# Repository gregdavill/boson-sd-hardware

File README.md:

# bosonFrameGrabber

	Project Stage: Basic MVP achieved

A Small FPGA based board. Designed to connect to a FLIR Boson Camera, and save images from the camera to a microSD card.

hw 1_02 is the latest functionaly hardware that fits just behind the back of the Boson. (Pictured Above)

## Project Status:
 + hw 1_01 working (reached limitations of FPGA)
 + hw 1_02 status
   + designed/assembled prototypes
   + Working on Firmware on a softcore riscv CPU. 
   + Basic capture system implmented in rtl.
   + Basic driver for SD card access using FatFS and SD-controller.

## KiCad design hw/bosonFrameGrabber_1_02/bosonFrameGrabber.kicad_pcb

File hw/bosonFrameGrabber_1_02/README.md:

# bosonFrameGrabber v1.02

	Project Stage: Still in Development

A Small FPGA based board. Designed to connect to a FLIR Boson Camera, and save images from the camera to a microSD card.

## Hardware

* ECP5 in csBGA285 package
* 64Mb/128Mb HyperRAM
* 8Mb QSPI Memory
* MicroSD socket
* 24Mhz MEMs Oscillator
* JST GH SM06 locking Data/Power connector
* JTAG exposed via pogo pin pads.
* 2x 5V tolerant I/Os on connector
* 1x LED

Prototype Limitations:
* 3.3V only! (Integrated LDOs handle FPGA rails, but input power is connected directly to the Boson)

## Prototype

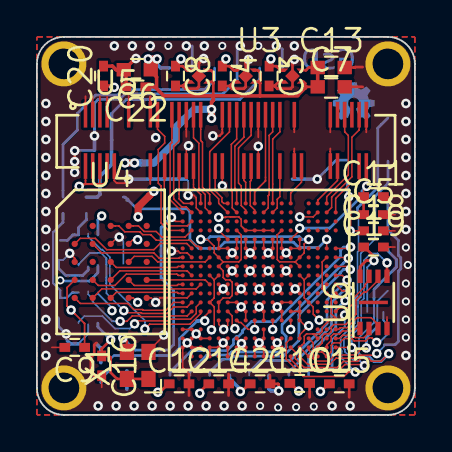
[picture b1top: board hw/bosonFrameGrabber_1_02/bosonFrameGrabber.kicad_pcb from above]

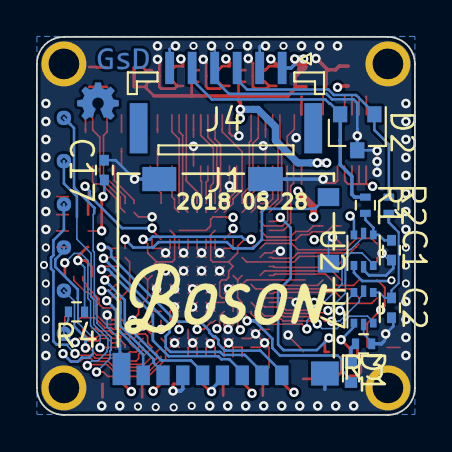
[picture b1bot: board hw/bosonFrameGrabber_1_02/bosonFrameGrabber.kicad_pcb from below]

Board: 4 copper layers, 21.0 x 21.0 mm, 40 parts (13 on the bottom side), 67 nets.

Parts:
C1, C2: 100pF; C_0402
C3, C4, C8: 1uF; C_0402
C5, C9, C10, C11, C12, C14, C15, C16, C17, C18, C19, C20, C21, C22: 100nF; C_0402
C6, C7, C13: 10uF; C_0603
D1: LED; LED_0402
D2: D_TVS_x2_AAC; SOT-23
J1: JST GH Series; JST_GH_BM06B-GHS-TBT_06x1.25mm_Straight
J4: MicroSD; 1040310811
R1, R2: 100R; R_0402
R3, R4: 10k; R_0402
U1: TLV70725; X2SON
U2, U7: SN74LVC1T45; SOT-666
U3: ECP5U25; csBGA_132
U4: S27KS0641; BGA_24
U5: Boson; DF40_80Pin
U6: AT25SF081; DFN-8-1EP_3x2mm_Pitch0.5mm
U8: TLV71718; X2SON
U9: TLV73311; X2SON
X1: ASDMB; Oscillator_SMD_SeikoEpson_SG210-4pin_2.5x2.0mm

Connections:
16MHZ_IN: U3.C1, X1.3
+1V1: C8.1, C10.1, C14.1, C17.1, C18.1, C20.1, U3.D8, U3.D9, U3.D10, U3.D11, U3.J4, U3.J5, U3.J14, U3.J15, U3.M4, U3.M15, U3.P7, U3.P9, U3.P11, U9.1
+1V8: C4.1, C9.1, C12.1, C16.1, U2.1, U3.D7, U3.D12, U3.G5, U3.G14, U3.H5, U3.H14, U3.M5, U3.N5, U4.B4, U4.D1, U4.E4, U7.1, U8.1, X1.1, X1.4
+2V5: C3.1, C5.1, C11.1, C15.1, U1.1, U3.E6, U3.E13, U3.N6, U3.P13
+3V3: C6.1, C7.1, C13.1, C19.1, C21.1, C22.1, J1.1, J4.4, R4.1, U1.3, U1.4, U2.6, U3.M14, U3.N13, U3.N14, U3.P14, U3.T14, U5.2, U5.4, U5.6, U5.8, U6.8, U7.6, U8.3, U8.4, U9.3, U9.4
BOSON_CK: U3.A11, U5.55
BOSON_DATA0: U3.B17, U5.77
BOSON_DATA1: U3.A13, U5.62
BOSON_DATA2: U3.A9, U5.51
BOSON_DATA3: U3.B11, U5.56
BOSON_DATA4: U3.B2, U5.27
BOSON_DATA5: U3.A2, U5.28
BOSON_DATA6: U3.A3, U5.32
BOSON_DATA7: U3.B4, U5.31
BOSON_DATA8: U3.B1, U5.25
BOSON_DATA9: U3.A8, U5.46
BOSON_DATA10: U3.A7, U5.45
BOSON_DATA11: U3.B9, U5.48
BOSON_DATA12: U3.B8, U5.47
BOSON_DATA13: U3.B6, U5.41
BOSON_DATA14: U3.D1, U5.21
BOSON_DATA15: U3.A6, U5.38
BOSON_DATA_EN: U3.B18, U5.78
BOSON_EXTSYNC: U3.A16, U5.72
BOSON_HSYNC: U3.A17, U5.73
BOSON_RESET: U3.C2, U5.24
BOSON_RXD: U3.A4, U5.33
BOSON_TXD: U3.B7, U5.43
BOSON_VSYNC: U3.B10, U5.53
FPGA_RESET: R4.2, U3.T15, U3.V17
GND: C1.2, C2.2, C3.2, C4.2, C5.2, C6.2, C7.2, C8.2, C9.2, C10.2, C11.2, C12.2, C13.2, C14.2, C15.2, C16.2, C17.2, C18.2, C19.2, C20.2, C21.2, C22.2, D2.3, J1.2, J1.4, J1.6, J4.6, J4.9, J4.10, R3.1, U1.2, U2.2, U3.B3, U3.B16, U3.E5, U3.E7, U3.E8, U3.E9, U3.E10, U3.E11, U3.E12, U3.E14, U3.F5, U3.F6, U3.F7, U3.F8, U3.F9, U3.F10, U3.F11, U3.F12, U3.F13, U3.F14, U3.G2, U3.G6, U3.G7, U3.G8, U3.G9, U3.G10, U3.G11, U3.G12, U3.G13, U3.G17, U3.H6, U3.H7, U3.H8, U3.H9, U3.H10, U3.H11, U3.H12, U3.H13, U3.J6, U3.J7, U3.J8, U3.J9, U3.J10, U3.J11, U3.J12, U3.J13, U3.K5, U3.K6, U3.K7, U3.K8, U3.K9, U3.K10, U3.K11, U3.K12, U3.K13, U3.K14, U3.L2, U3.L5, U3.L6, U3.L7, U3.L8, U3.L9, U3.L10, U3.L11, U3.L12, U3.L13, U3.L14, U3.L17, U3.M6, U3.M7, U3.M8, U3.M9, U3.M10, U3.M11, U3.M12, U3.M13, U3.N7, U3.N8, U3.N9, U3.N10, U3.N11, U3.N12, U3.P5, U3.P6, U3.P8, U3.P10, U3.P12, U3.R1, U3.R2, U3.R3, U3.R10, U3.T1, U3.T2, U3.T3, U3.T4, U3.T5, U3.T6, U3.T7, U3.T8, U3.T9, U3.T10, U3.T11, U3.T12, U3.T16, U3.U1, U3.U2, U3.U3, U3.U4, U3.U5, U3.U6, U3.U7, U3.U8, U3.U9, U3.U10, U3.U11, U3.U12, U3.U14, U3.V4, U3.V5, U3.V6, U3.V7, U3.V8, U3.V9, U3.V10, U3.V15, U4.B3, U4.C1, U4.E5, U5.1, U5.3, U5.5, U5.7, U5.10, U5.13, U5.19, U5.20, U5.29, U5.30, U5.39, U5.40, U5.49, U5.50, U5.59, U5.60, U5.69, U5.70, U5.79, U6.4, U7.2, U8.2, U9.2, X1.2
HYPERBUS_CK: U3.G1, U4.B2
HYPERBUS_CK#: U3.F2, U4.B1
HYPERBUS_CS#: U3.F3, U4.A3
HYPERBUS_DQ0: U3.J2, U4.D3
HYPERBUS_DQ1: U3.J1, U4.D2
HYPERBUS_DQ2: U3.G4, U4.C4
HYPERBUS_DQ3: U3.K1, U4.D4
HYPERBUS_DQ4: U3.K4, U4.D5
HYPERBUS_DQ5: U3.L1, U4.E3
HYPERBUS_DQ6: U3.K3, U4.E2
HYPERBUS_DQ7: U3.M1, U4.E1
HYPERBUS_RESET#: U3.D2, U4.A4
HYPERBUS_RWDS: U3.H1, U4.C3
IO_A: D2.2, J1.5, R1.1
IO_A_DIR: U2.5, U3.N3
IO_A_INTERNAL: U2.3, U3.M2
IO_B: D2.1, J1.3, R2.1
IO_B_DIR: U3.N2, U7.5
IO_B_INTERNAL: U3.M3, U7.3
LED_A: D1.2, U3.N4
unnamed: C1.1, R1.2, U2.4
unnamed: C2.1, R2.2, U7.4
unnamed: D1.1, R3.2
QSPI_D2: U3.R18, U6.3
QSPI_D3: U3.N18, U6.7
SD_CD: J4.11, U3.F17
SD_CK: J4.5, U3.J18
SD_CMD: J4.3, U3.H18
SD_DAT0: J4.7, U3.K18
SD_DAT1: J4.8, U3.L18
SD_DAT2: J4.1, U3.F18
SD_DAT3: J4.2, U3.G18
SPI_CONFIG_MISO: U3.T18, U6.2
SPI_CONFIG_MOSI: U3.U18, U6.5
SPI_CONFIG_SCK: U3.U16, U6.6
SPI_CONFIG_SS: U3.U17, U6.1

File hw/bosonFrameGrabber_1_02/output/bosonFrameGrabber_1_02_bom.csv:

Reference, Quantity, Value, Footprint, Datasheet, PN, SN-DK
C1 C2 ,2,"100pF","Capacitors_SMD:C_0402","","C0402C101J3GACTU","399-1022-1-ND"
C3 C4 C8 ,3,"1uF","Capacitors_SMD:C_0402","","CGB2A1X5R1E105K033BC","445-13185-1-ND"
C10 C11 C12 C14 C15 C16 C17 C18 C19 C20 C21 C22 C5 C9 ,14,"100nF","Capacitors_SMD:C_0402","","CL05B104KP5NNNC","1276-1002-1-ND"
C13 C6 C7 ,3,"10uF","Capacitors_SMD:C_0603","","C1608X5R1A106K080AC","445-7486-1-ND"
D1 ,1,"LED","LEDs:LED_0603","","APHHS1005SYCK ","754-1105-1-ND"
D2 ,1,"D_TVS_x2_AAC","TO_SOT_Packages_SMD:SOT-23","https://en.wikipedia.org/wiki/Transient-voltage-suppression_diode","PESD5V0U2BT,215","1727-3936-1-ND"
J1 ,1,"JST GH Series","Connectors_JST:JST_GH_BM06B-GHS-TBT_06x1.25mm_Straight","~","BM06B-GHS-TBT(LF)(SN)(N) ","455-1582-1-ND"
J4 ,1,"MicroSD","bosonFrameGrabber:1040310811","~","1040310811"," WM6357CT-ND"
R1 R2 ,2,"100R","Resistors_SMD:R_0402","","RT0402FRE07100RL","YAG3342CT-ND"
R3 R4 ,2,"10k","Resistors_SMD:R_0402","","ERA-2AED103X","P10KDECT-ND"
U1 ,1,"TLV70725","bosonFrameGrabber:X2SON","","TLV70725PDQNT ","296-34993-1-ND"
U3 ,1,"ECP5U25","","","LFE5UM-25F-6MG285C "," LFE5UM-25F-6MG285C-ND "
U4 ,1,"S27KS0641","bosonFrameGrabber:BGA_24","","S27KS0641DPBHI020","428-3858-ND"
U5 ,1,"Boson","","","DF40HC(4.0)-80DS-0.4V(51)","H11919CT-ND"
U6 ,1,"AT25SF081","Housings_DFN_QFN:DFN-8-1EP_3x2mm_Pitch0.5mm","","AT25SF081-MAHD-T","1265-1275-1-ND"
U2 U7 ,2,"SN74LVC1T45","TO_SOT_Packages_SMD:SOT-666","","SN74LVC1T45DRLR","296-20629-1-ND"
U8 ,1,"TLV71718","bosonFrameGrabber:X2SON","","TLV71718PDQNR ","296-36775-1-ND"
U9 ,1,"TLV73311","bosonFrameGrabber:X2SON","","TLV73311PDQNT ","296-38619-1-ND"
X1 ,1,"ASDMB","Oscillators:Oscillator_SMD_SeikoEpson_SG210-4pin_2.5x2.0mm","http://www.abracon.com/Oscillators/ASV.pdf","SIT8008BI-71-18E-24.000000G","1473-30509-1-ND"

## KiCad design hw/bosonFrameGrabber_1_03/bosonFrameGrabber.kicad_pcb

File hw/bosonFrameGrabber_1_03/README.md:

# bosonFrameGrabber 1_03

	Development BigBoard (Do not use! known errata)

Due to supply issues of the ECP5 in cs285 I developed this PCB to start work on firmware. Despite many errata the board was functional (after mods) and did aid in fw development.

## Errata
* 1V8 line shorted by a via (didn't run DRC)
* SysConfig pins are not correct for loading bitstream from SPI.
* Incorrect pins connected to QSPI.
* 3V3 not connected to backlinght DCDC

## Hardware

* ECP5 
* 8MB/16MB HyperRAM: high density, low pin count.
* 1MB QSPI Memory (XSON 3x2 package)
* MicroSD socket
* MEMs Oscillator
* JST GH SM06 locking Data/Power connector
* JTAG on GH SM06
* 2x 5V tolerant I/Os on connector
* 1x LED
* 240x240 IPS LCD. (used on NANO v6, MIPI interface)

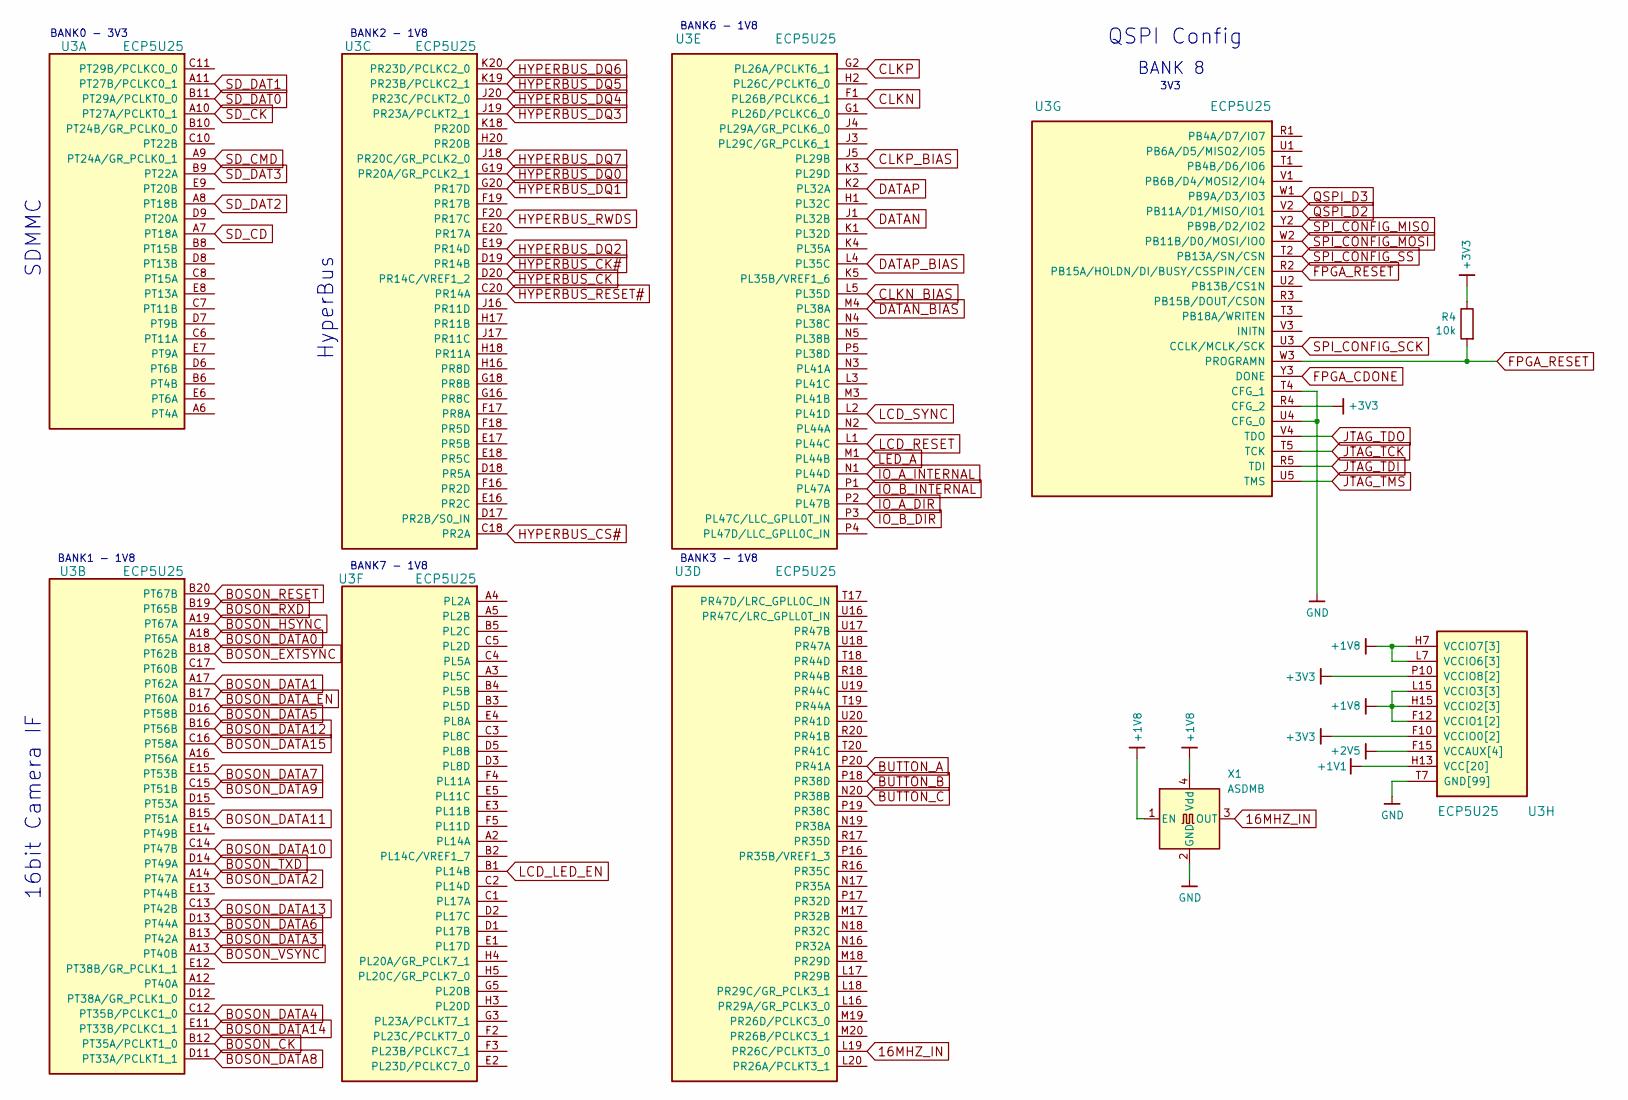
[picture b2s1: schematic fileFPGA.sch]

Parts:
R4: 10k; R_0402
U3: ECP5U25
X1: ASDMB; Oscillator_SMD_SeikoEpson_SG210-4pin_2.5x2.0mm

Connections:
16MHZ_IN: U3.L19 (PR26C/PCLKT3_0), X1.3 (OUT)
+1V1: U3.H8 (VCC[20]), U3.H9 (VCC[20]), U3.H10 (VCC[20]), U3.H11 (VCC[20]), U3.H12 (VCC[20]), U3.H13 (VCC[20]), U3.J8 (VCC[20]), U3.J13 (VCC[20]), U3.K8 (VCC[20]), U3.K13 (VCC[20]), U3.L8 (VCC[20]), U3.L13 (VCC[20]), U3.M8 (VCC[20]), U3.M13 (VCC[20]), U3.N8 (VCC[20]), U3.N9 (VCC[20]), U3.N10 (VCC[20]), U3.N11 (VCC[20]), U3.N12 (VCC[20]), U3.N13 (VCC[20]); also elsewhere on the board
+1V8: U3.F11 (VCCIO1[2]), U3.F12 (VCCIO1[2]), U3.H6 (VCCIO7[3]), U3.H7 (VCCIO7[3]), U3.H14 (VCCIO2[3]), U3.H15 (VCCIO2[3]), U3.J6 (VCCIO7[3]), U3.J15 (VCCIO2[3]), U3.L6 (VCCIO6[3]), U3.L7 (VCCIO6[3]), U3.L14 (VCCIO3[3]), U3.L15 (VCCIO3[3]), U3.M6 (VCCIO6[3]), U3.M15 (VCCIO3[3]), X1.1 (EN), X1.4 (Vdd); also elsewhere on the board
+2V5: U3.F6 (VCCAUX[4]), U3.F15 (VCCAUX[4]), U3.P6 (VCCAUX[4]), U3.P15 (VCCAUX[4]); also elsewhere on the board
+3V3: R4.1, U3.F9 (VCCIO0[2]), U3.F10 (VCCIO0[2]), U3.P9 (VCCIO8[2]), U3.P10 (VCCIO8[2]), U3.R4 (CFG_2); also elsewhere on the board
BOSON_CK: U3.B12 (PT35A/PCLKT1_0); also elsewhere on the board
BOSON_DATA0: U3.A18 (PT65A); also elsewhere on the board
BOSON_DATA1: U3.A17 (PT62A); also elsewhere on the board
BOSON_DATA2: U3.A14 (PT47A); also elsewhere on the board
BOSON_DATA3: U3.B13 (PT42A); also elsewhere on the board
BOSON_DATA4: U3.C12 (PT35B/PCLKC1_0); also elsewhere on the board
BOSON_DATA5: U3.D16 (PT58B); also elsewhere on the board
BOSON_DATA6: U3.D13 (PT44A); also elsewhere on the board
BOSON_DATA7: U3.E15 (PT53B); also elsewhere on the board
BOSON_DATA8: U3.D11 (PT33A/PCLKT1_1); also elsewhere on the board
BOSON_DATA9: U3.C15 (PT51B); also elsewhere on the board
BOSON_DATA10: U3.C14 (PT47B); also elsewhere on the board
BOSON_DATA11: U3.B15 (PT51A); also elsewhere on the board
BOSON_DATA12: U3.B16 (PT56B); also elsewhere on the board
BOSON_DATA13: U3.C13 (PT42B); also elsewhere on the board
BOSON_DATA14: U3.E11 (PT33B/PCLKC1_1); also elsewhere on the board
BOSON_DATA15: U3.C16 (PT58A); also elsewhere on the board
BOSON_DATA_EN: U3.B17 (PT60A); also elsewhere on the board
BOSON_EXTSYNC: U3.B18 (PT62B); also elsewhere on the board
BOSON_HSYNC: U3.A19 (PT67A); also elsewhere on the board
BOSON_RESET: U3.B20 (PT67B); also elsewhere on the board
BOSON_RXD: U3.B19 (PT65B); also elsewhere on the board
BOSON_TXD: U3.D14 (PT49A); also elsewhere on the board
BOSON_VSYNC: U3.A13 (PT40B); also elsewhere on the board
BUTTON_A: U3.P20 (PR41A); also elsewhere on the board
BUTTON_B: U3.P18 (PR38D); also elsewhere on the board
BUTTON_C: U3.N20 (PR38B); also elsewhere on the board
CLKN: U3.F1 (PL26B/PCLKC6_1); also elsewhere on the board
CLKN_BIAS: U3.L5 (PL35D); also elsewhere on the board
CLKP: U3.G2 (PL26A/PCLKT6_1); also elsewhere on the board
CLKP_BIAS: U3.J5 (PL29B); also elsewhere on the board
DATAN: U3.J1 (PL32B); also elsewhere on the board
DATAN_BIAS: U3.M4 (PL38A); also elsewhere on the board
DATAP: U3.K2 (PL32A); also elsewhere on the board
DATAP_BIAS: U3.L4 (PL35C); also elsewhere on the board
FPGA_CDONE: U3.Y3 (DONE)
FPGA_RESET: R4.2, U3.R2 (PB15A/HOLDN/DI/BUSY/CSSPIN/CEN), U3.W3 (PROGRAMN)
GND: U3.B7 (GND[99]), U3.B14 (GND[99]), U3.C19 (GND[99]), U3.D4 (GND[99]), U3.F7 (GND[99]), U3.F8 (GND[99]), U3.F13 (GND[99]), U3.F14 (GND[99]), U3.G4 (GND[99]), U3.G6 (GND[99]), U3.G7 (GND[99]), U3.G8 (GND[99]), U3.G9 (GND[99]), U3.G10 (GND[99]), U3.G11 (GND[99]), U3.G12 (GND[99]), U3.G13 (GND[99]), U3.G14 (GND[99]), U3.G15 (GND[99]), U3.G17 (GND[99]), U3.H19 (GND[99]), U3.J2 (GND[99]), U3.J7 (GND[99]), U3.J9 (GND[99]), U3.J10 (GND[99]), U3.J11 (GND[99]), U3.J12 (GND[99]), U3.J14 (GND[99]), U3.K6 (GND[99]), U3.K7 (GND[99]), U3.K9 (GND[99]), U3.K10 (GND[99]), U3.K11 (GND[99]), U3.K12 (GND[99]), U3.K14 (GND[99]), U3.K15 (GND[99]), U3.L9 (GND[99]), U3.L10 (GND[99]), U3.L11 (GND[99]), U3.L12 (GND[99]), U3.M2 (GND[99]), U3.M7 (GND[99]), U3.M9 (GND[99]), U3.M10 (GND[99]), U3.M11 (GND[99]), U3.M12 (GND[99]), U3.M14 (GND[99]), U3.M16 (GND[99]), U3.N6 (GND[99]), U3.N7 (GND[99]), U3.N14 (GND[99]), U3.N15 (GND[99]), U3.P7 (GND[99]), U3.P8 (GND[99]), U3.P11 (GND[99]), U3.P12 (GND[99]), U3.P13 (GND[99]), U3.P14 (GND[99]), U3.R19 (GND[99]), U3.T4 (CFG_1), U3.T6 (GND[99]), U3.T7 (GND[99]), U3.T8 (GND[99]), U3.T9 (GND[99]), U3.T10 (GND[99]), U3.U4 (CFG_0), U3.U6 (GND[99]), U3.U7 (GND[99]), U3.U8 (GND[99]), U3.U9 (GND[99]), U3.U10 (GND[99]), U3.U11 (GND[99]), U3.U12 (GND[99]), U3.U13 (GND[99]), U3.U14 (GND[99]), U3.V5 (GND[99]), U3.V6 (GND[99]), U3.V7 (GND[99]), U3.V8 (GND[99]), U3.V9 (GND[99]), U3.V10 (GND[99]), U3.V11 (GND[99]), U3.V12 (GND[99]), U3.V13 (GND[99]), U3.V14 (GND[99]), U3.V15 (GND[99]), U3.V16 (GND[99]), U3.V19 (GND[99]), U3.V20 (GND[99]), U3.W6 (GND[99]), U3.W7 (GND[99]), U3.W12 (GND[99]), U3.W15 (GND[99]), U3.W16 (GND[99]), U3.W19 (GND[99]), U3.Y5 (GND[99]), U3.Y6 (GND[99]), U3.Y7 (GND[99]), U3.Y8 (GND[99]), U3.Y11 (GND[99]), U3.Y12 (GND[99]), X1.2 (GND); also elsewhere on the board
HYPERBUS_CK: U3.D20 (PR14C/VREF1_2); also elsewhere on the board
HYPERBUS_CK#: U3.D19 (PR14B); also elsewhere on the board
HYPERBUS_CS#: U3.C18 (PR2A); also elsewhere on the board
HYPERBUS_DQ0: U3.G19 (PR20A/GR_PCLK2_1); also elsewhere on the board
HYPERBUS_DQ1: U3.G20 (PR17D); also elsewhere on the board
HYPERBUS_DQ2: U3.E19 (PR14D); also elsewhere on the board
HYPERBUS_DQ3: U3.J19 (PR23A/PCLKT2_1); also elsewhere on the board
HYPERBUS_DQ4: U3.J20 (PR23C/PCLKT2_0); also elsewhere on the board
HYPERBUS_DQ5: U3.K19 (PR23B/PCLKC2_1); also elsewhere on the board
HYPERBUS_DQ6: U3.K20 (PR23D/PCLKC2_0); also elsewhere on the board
HYPERBUS_DQ7: U3.J18 (PR20C/GR_PCLK2_0); also elsewhere on the board
HYPERBUS_RESET#: U3.C20 (PR14A); also elsewhere on the board
HYPERBUS_RWDS: U3.F20 (PR17C); also elsewhere on the board
IO_A_DIR: U3.P2 (PL47B); also elsewhere on the board
IO_A_INTERNAL: U3.N1 (PL44D); also elsewhere on the board
IO_B_DIR: U3.P3 (PL47C/LLC_GPLL0T_IN); also elsewhere on the board
IO_B_INTERNAL: U3.P1 (PL47A); also elsewhere on the board
JTAG_TCK: U3.T5 (TCK); also elsewhere on the board
JTAG_TDI: U3.R5 (TDI); also elsewhere on the board
JTAG_TDO: U3.V4 (TDO); also elsewhere on the board
JTAG_TMS: U3.U5 (TMS); also elsewhere on the board
LCD_LED_EN: U3.B1 (PL14B); also elsewhere on the board
LCD_RESET: U3.L1 (PL44C); also elsewhere on the board
LCD_SYNC: U3.L2 (PL41D); also elsewhere on the board
LED_A: U3.M1 (PL44B); also elsewhere on the board
QSPI_D2: U3.V2 (PB11A/D1/MISO/IO1); also elsewhere on the board
QSPI_D3: U3.W1 (PB9A/D3/IO3); also elsewhere on the board
SD_CD: U3.A7 (PT18A); also elsewhere on the board
SD_CK: U3.A10 (PT27A/PCLKT0_1); also elsewhere on the board
SD_CMD: U3.A9 (PT24A/GR_PCLK0_1); also elsewhere on the board
SD_DAT0: U3.B11 (PT29A/PCLKT0_0); also elsewhere on the board
SD_DAT1: U3.A11 (PT27B/PCLKC0_1); also elsewhere on the board
SD_DAT2: U3.A8 (PT18B); also elsewhere on the board
SD_DAT3: U3.B9 (PT22A); also elsewhere on the board
SPI_CONFIG_MISO: U3.Y2 (PB9B/D2/IO2); also elsewhere on the board
SPI_CONFIG_MOSI: U3.W2 (PB11B/D0/MOSI/IO0); also elsewhere on the board
SPI_CONFIG_SCK: U3.U3 (CCLK/MCLK/SCK); also elsewhere on the board
SPI_CONFIG_SS: U3.T2 (PB13A/SN/CSN); also elsewhere on the board

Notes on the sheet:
BANK 8
3V3
QSPI Config
HyperBus
SDMMC
16bit Camera IF
BANK0 - 3V3
BANK1 - 1V8
BANK7 - 1V8
BANK2 - 1V8
BANK6 - 1V8
BANK3 - 1V8

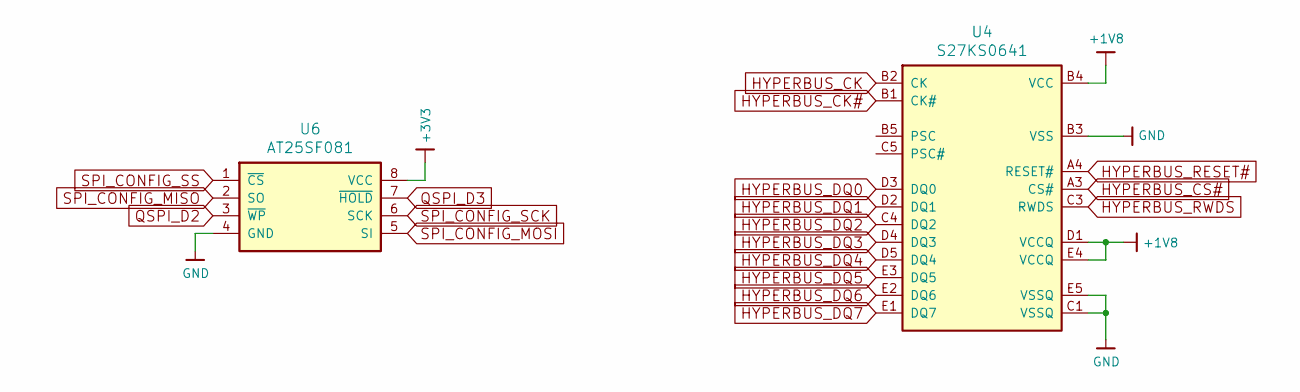
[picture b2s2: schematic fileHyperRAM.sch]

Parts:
U4: S27KS0641; BGA_24
U6: AT25SF081; DFN-8-1EP_3x2mm_Pitch0.5mm

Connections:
+1V8: U4.B4 (VCC), U4.D1 (VCCQ), U4.E4 (VCCQ); also elsewhere on the board
+3V3: U6.8 (VCC); also elsewhere on the board
GND: U4.B3 (VSS), U4.C1 (VSSQ), U4.E5 (VSSQ), U6.4 (GND); also elsewhere on the board
HYPERBUS_CK: U4.B2 (CK); also elsewhere on the board
HYPERBUS_CK#: U4.B1 (CK#); also elsewhere on the board
HYPERBUS_CS#: U4.A3 (CS#); also elsewhere on the board
HYPERBUS_DQ0: U4.D3 (DQ0); also elsewhere on the board
HYPERBUS_DQ1: U4.D2 (DQ1); also elsewhere on the board
HYPERBUS_DQ2: U4.C4 (DQ2); also elsewhere on the board
HYPERBUS_DQ3: U4.D4 (DQ3); also elsewhere on the board
HYPERBUS_DQ4: U4.D5 (DQ4); also elsewhere on the board
HYPERBUS_DQ5: U4.E3 (DQ5); also elsewhere on the board
HYPERBUS_DQ6: U4.E2 (DQ6); also elsewhere on the board
HYPERBUS_DQ7: U4.E1 (DQ7); also elsewhere on the board
HYPERBUS_RESET#: U4.A4 (RESET#); also elsewhere on the board
HYPERBUS_RWDS: U4.C3 (RWDS); also elsewhere on the board
QSPI_D2: U6.3 (~WP); also elsewhere on the board
QSPI_D3: U6.7 (~HOLD); also elsewhere on the board
SPI_CONFIG_MISO: U6.2 (SO); also elsewhere on the board
SPI_CONFIG_MOSI: U6.5 (SI); also elsewhere on the board
SPI_CONFIG_SCK: U6.6 (SCK); also elsewhere on the board
SPI_CONFIG_SS: U6.1 (~CS); also elsewhere on the board

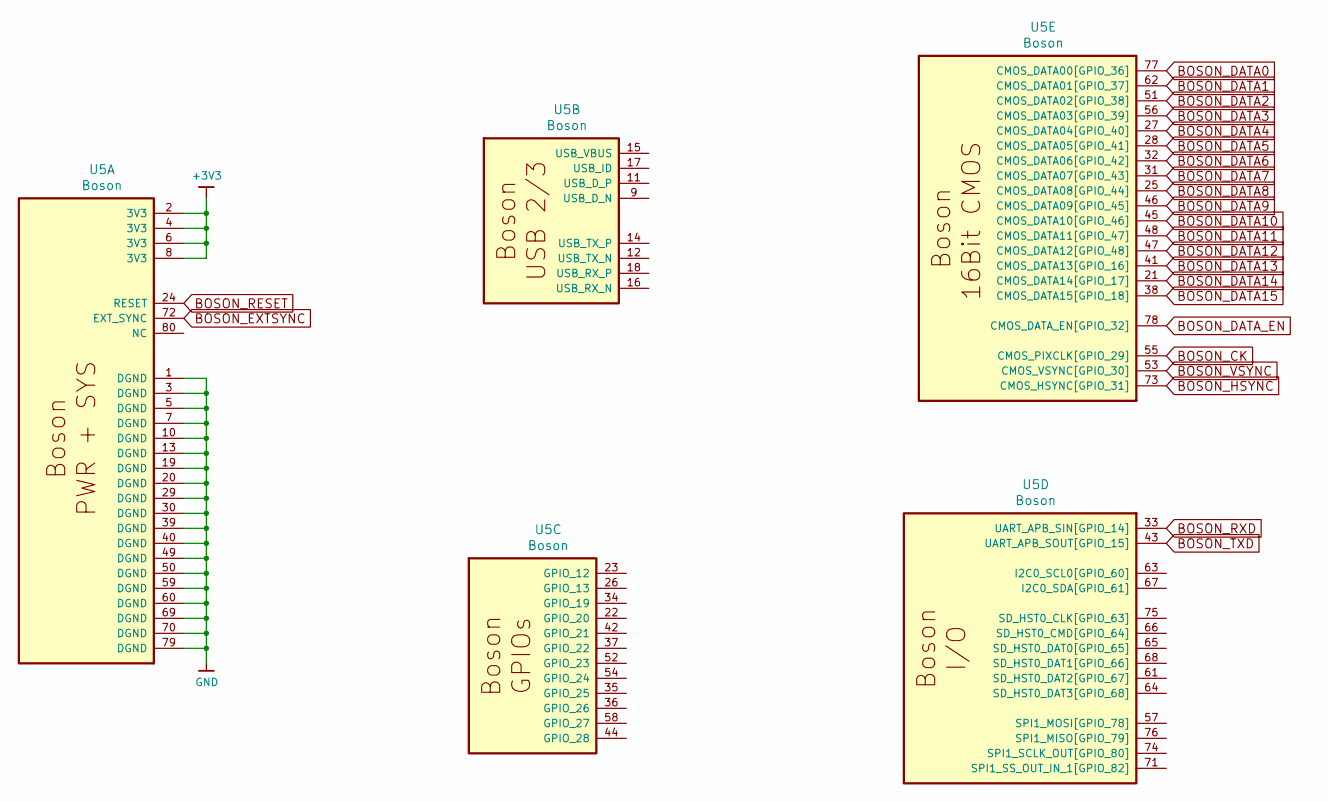
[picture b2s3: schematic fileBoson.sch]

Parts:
U5: Boson

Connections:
+3V3: U5.2 (3V3), U5.4 (3V3), U5.6 (3V3), U5.8 (3V3); also elsewhere on the board
BOSON_CK: U5.55 (CMOS_PIXCLK[GPIO_29]); also elsewhere on the board
BOSON_DATA0: U5.77 (CMOS_DATA00[GPIO_36]); also elsewhere on the board
BOSON_DATA1: U5.62 (CMOS_DATA01[GPIO_37]); also elsewhere on the board
BOSON_DATA2: U5.51 (CMOS_DATA02[GPIO_38]); also elsewhere on the board
BOSON_DATA3: U5.56 (CMOS_DATA03[GPIO_39]); also elsewhere on the board
BOSON_DATA4: U5.27 (CMOS_DATA04[GPIO_40]); also elsewhere on the board
BOSON_DATA5: U5.28 (CMOS_DATA05[GPIO_41]); also elsewhere on the board
BOSON_DATA6: U5.32 (CMOS_DATA06[GPIO_42]); also elsewhere on the board
BOSON_DATA7: U5.31 (CMOS_DATA07[GPIO_43]); also elsewhere on the board
BOSON_DATA8: U5.25 (CMOS_DATA08[GPIO_44]); also elsewhere on the board
BOSON_DATA9: U5.46 (CMOS_DATA09[GPIO_45]); also elsewhere on the board
BOSON_DATA10: U5.45 (CMOS_DATA10[GPIO_46]); also elsewhere on the board
BOSON_DATA11: U5.48 (CMOS_DATA11[GPIO_47]); also elsewhere on the board
BOSON_DATA12: U5.47 (CMOS_DATA12[GPIO_48]); also elsewhere on the board
BOSON_DATA13: U5.41 (CMOS_DATA13[GPIO_16]); also elsewhere on the board
BOSON_DATA14: U5.21 (CMOS_DATA14[GPIO_17]); also elsewhere on the board
BOSON_DATA15: U5.38 (CMOS_DATA15[GPIO_18]); also elsewhere on the board
BOSON_DATA_EN: U5.78 (CMOS_DATA_EN[GPIO_32]); also elsewhere on the board
BOSON_EXTSYNC: U5.72 (EXT_SYNC); also elsewhere on the board
BOSON_HSYNC: U5.73 (CMOS_HSYNC[GPIO_31]); also elsewhere on the board
BOSON_RESET: U5.24 (RESET); also elsewhere on the board
BOSON_RXD: U5.33 (UART_APB_SIN[GPIO_14]); also elsewhere on the board
BOSON_TXD: U5.43 (UART_APB_SOUT[GPIO_15]); also elsewhere on the board
BOSON_VSYNC: U5.53 (CMOS_VSYNC[GPIO_30]); also elsewhere on the board
GND: U5.1 (DGND), U5.3 (DGND), U5.5 (DGND), U5.7 (DGND), U5.10 (DGND), U5.13 (DGND), U5.19 (DGND), U5.20 (DGND), U5.29 (DGND), U5.30 (DGND), U5.39 (DGND), U5.40 (DGND), U5.49 (DGND), U5.50 (DGND), U5.59 (DGND), U5.60 (DGND), U5.69 (DGND), U5.70 (DGND), U5.79 (DGND); also elsewhere on the board

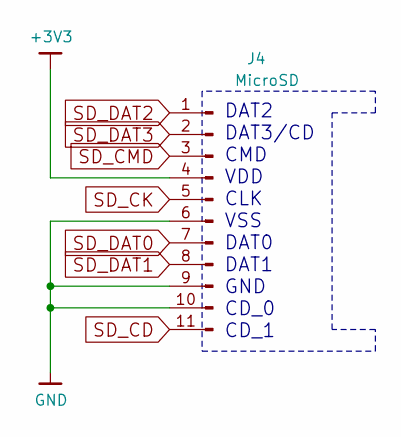
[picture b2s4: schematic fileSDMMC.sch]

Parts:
J4: MicroSD; 1040310811

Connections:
+3V3: J4.4; also elsewhere on the board
GND: J4.6, J4.9, J4.10; also elsewhere on the board
SD_CD: J4.11; also elsewhere on the board
SD_CK: J4.5; also elsewhere on the board
SD_CMD: J4.3; also elsewhere on the board
SD_DAT0: J4.7; also elsewhere on the board
SD_DAT1: J4.8; also elsewhere on the board
SD_DAT2: J4.1; also elsewhere on the board
SD_DAT3: J4.2; also elsewhere on the board

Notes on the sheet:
DAT2 DAT3/CD CMD VDD CLK VSS DAT0 DAT1 GND CD_0 CD_1

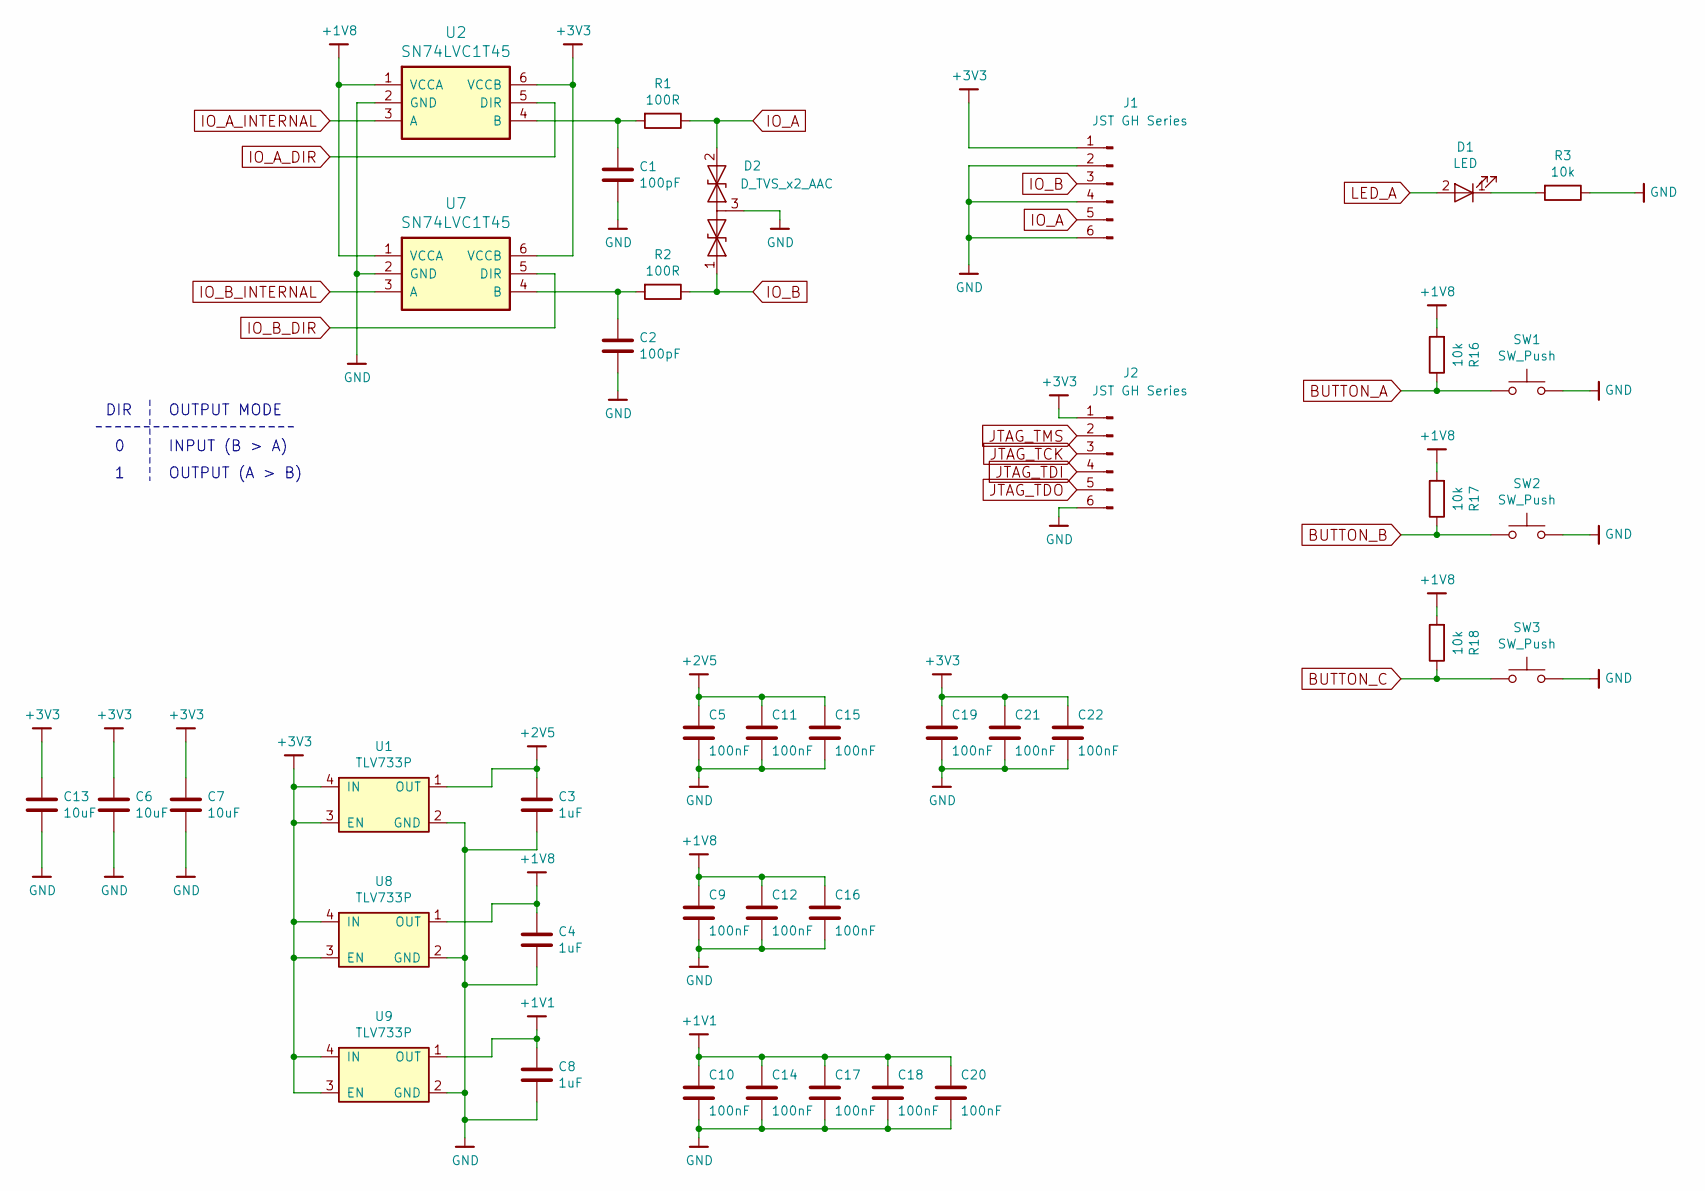
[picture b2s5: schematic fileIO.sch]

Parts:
C1, C2: 100pF; C_0402
C3, C4, C8: 1uF; C_0402
C5, C9, C10, C11, C12, C14, C15, C16, C17, C18, C19, C20, C21, C22: 100nF; C_0402
C6, C7, C13: 10uF; C_0603
D1: LED; LED_0603
D2: D_TVS_x2_AAC; SOT-23
J1, J2: JST GH Series; JST_GH_BM06B-GHS-TBT_06x1.25mm_Straight
R1, R2: 100R; R_0402
R3, R16, R17, R18: 10k; R_0402
SW1, SW2, SW3: SW_Push; SW_SPST_EVQP0
U1, U8, U9: TLV733P; X2SON
U2, U7: SN74LVC1T45; SOT-666

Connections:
+1V1: C8.1, C10.1, C14.1, C17.1, C18.1, C20.1, U9.1 (OUT); also elsewhere on the board
+1V8: C4.1, C9.1, C12.1, C16.1, R16.2, R17.2, R18.2, U2.1 (VCCA), U7.1 (VCCA), U8.1 (OUT); also elsewhere on the board
+2V5: C3.1, C5.1, C11.1, C15.1, U1.1 (OUT); also elsewhere on the board
+3V3: C6.1, C7.1, C13.1, C19.1, C21.1, C22.1, J1.1, J2.1, U1.3 (EN), U1.4 (IN), U2.6 (VCCB), U7.6 (VCCB), U8.3 (EN), U8.4 (IN), U9.3 (EN), U9.4 (IN); also elsewhere on the board
BUTTON_A: R16.1, SW1.1; also elsewhere on the board
BUTTON_B: R17.1, SW2.1; also elsewhere on the board
BUTTON_C: R18.1, SW3.1; also elsewhere on the board
GND: C1.2, C2.2, C3.2, C4.2, C5.2, C6.2, C7.2, C8.2, C9.2, C10.2, C11.2, C12.2, C13.2, C14.2, C15.2, C16.2, C17.2, C18.2, C19.2, C20.2, C21.2, C22.2, D2.3 (common), J1.2, J1.4, J1.6, J2.6, R3.1, SW1.2, SW2.2, SW3.2, U1.2 (GND), U2.2 (GND), U7.2 (GND), U8.2 (GND), U9.2 (GND); also elsewhere on the board
IO_A: D2.2 (A2), J1.5, R1.1
IO_A_DIR: U2.5 (DIR); also elsewhere on the board
IO_A_INTERNAL: U2.3 (A); also elsewhere on the board
IO_B: D2.1 (A1), J1.3, R2.1
IO_B_DIR: U7.5 (DIR); also elsewhere on the board
IO_B_INTERNAL: U7.3 (A); also elsewhere on the board
JTAG_TCK: J2.3; also elsewhere on the board
JTAG_TDI: J2.4; also elsewhere on the board
JTAG_TDO: J2.5; also elsewhere on the board
JTAG_TMS: J2.2; also elsewhere on the board
LED_A: D1.2 (A); also elsewhere on the board
unnamed: C1.1, R1.2, U2.4 (B)
unnamed: C2.1, R2.2, U7.4 (B)
unnamed: D1.1 (K), R3.2

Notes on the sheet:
DIR
INPUT (B > A)
OUTPUT (A > B)
OUTPUT MODE

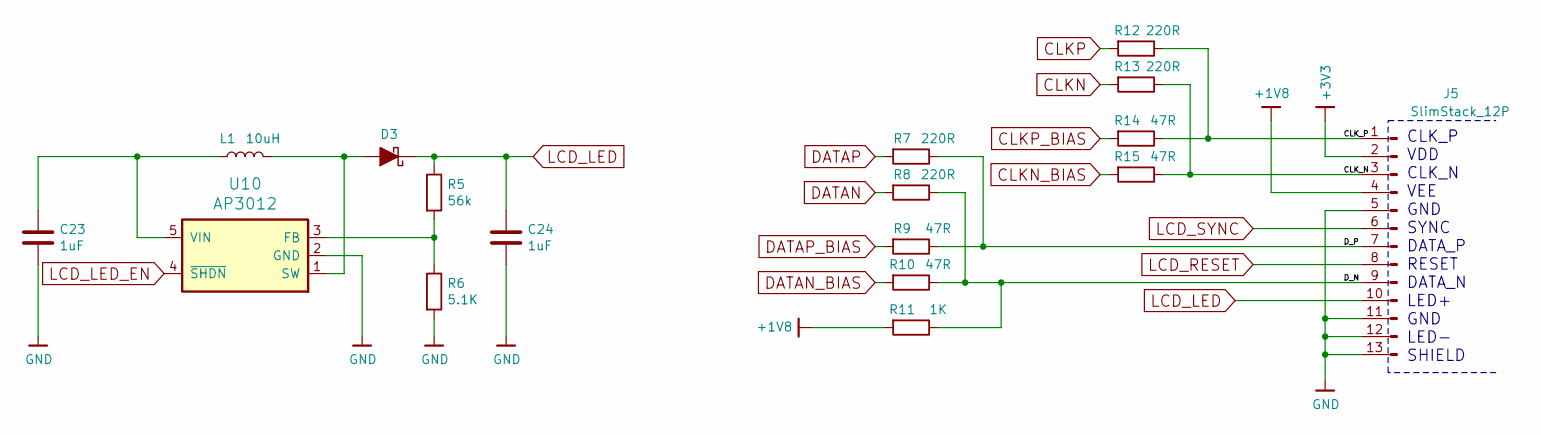
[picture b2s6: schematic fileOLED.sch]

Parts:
C23, C24: 1uF; C_0603
D3: D_Schottky_ALT; D_SOD-123F
J5: SlimStack_12P
L1: 10uH; L_0603
R5: 56k; R_0603
R6: 5.1K; R_0603
R7, R8, R12, R13: 220R; R_0402
R9, R10, R14, R15: 47R; R_0402
R11: 1K; R_0402
U10: AP3012; SOT-23-5

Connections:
+1V8: J5.4, R11.2; also elsewhere on the board
+3V3: J5.2; also elsewhere on the board
/sheetOLED/CLK_N: J5.3, R13.1, R15.1
/sheetOLED/CLK_P: J5.1, R12.1, R14.1
/sheetOLED/D_N: J5.9, R8.1, R10.1, R11.1
/sheetOLED/D_P: J5.7, R7.1, R9.1
CLKN: R13.2; also elsewhere on the board
CLKN_BIAS: R15.2; also elsewhere on the board
CLKP: R12.2; also elsewhere on the board
CLKP_BIAS: R14.2; also elsewhere on the board
DATAN: R8.2; also elsewhere on the board
DATAN_BIAS: R10.2; also elsewhere on the board
DATAP: R7.2; also elsewhere on the board
DATAP_BIAS: R9.2; also elsewhere on the board
GND: C23.2, C24.2, J5.5, J5.11, J5.12, J5.13, R6.2, U10.2 (GND); also elsewhere on the board
LCD_LED: C24.1, D3.1 (K), J5.10, R5.1
LCD_LED_EN: U10.4 (~SHDN); also elsewhere on the board
LCD_RESET: J5.8; also elsewhere on the board
LCD_SYNC: J5.6; also elsewhere on the board
unnamed: C23.1, L1.1, U10.5 (VIN)
unnamed: D3.2 (A), L1.2, U10.1 (SW)
unnamed: R5.2, R6.1, U10.3 (FB)

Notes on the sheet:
CLK_P VDD CLK_N VEE GND SYNC DATA_P RESET DATA_N LED+ GND LED- SHIELD

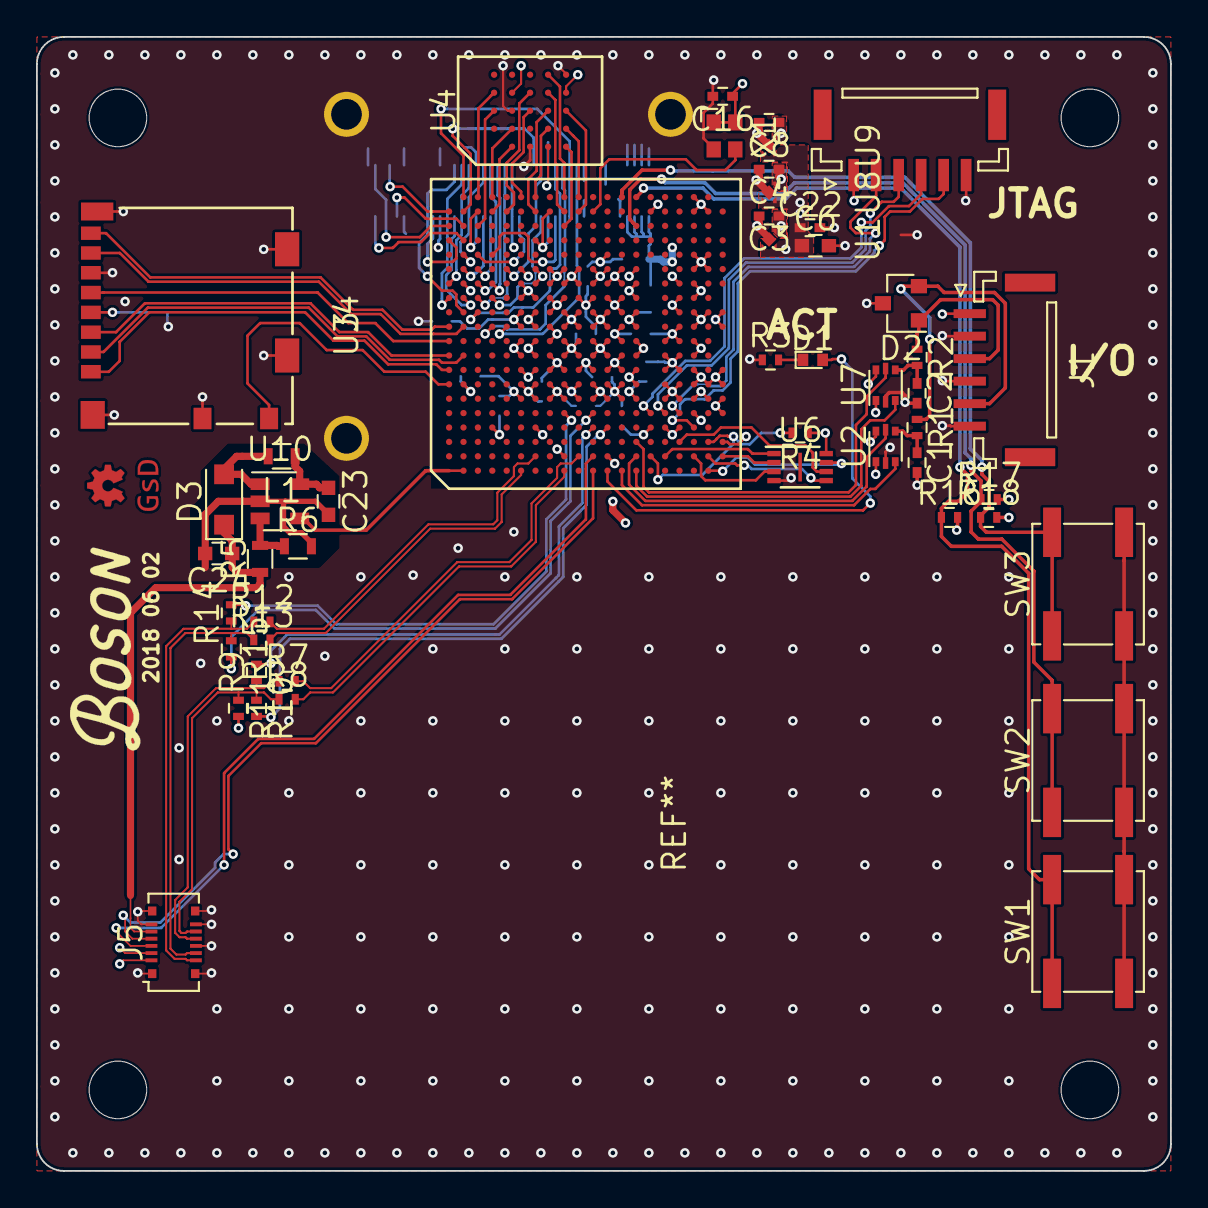
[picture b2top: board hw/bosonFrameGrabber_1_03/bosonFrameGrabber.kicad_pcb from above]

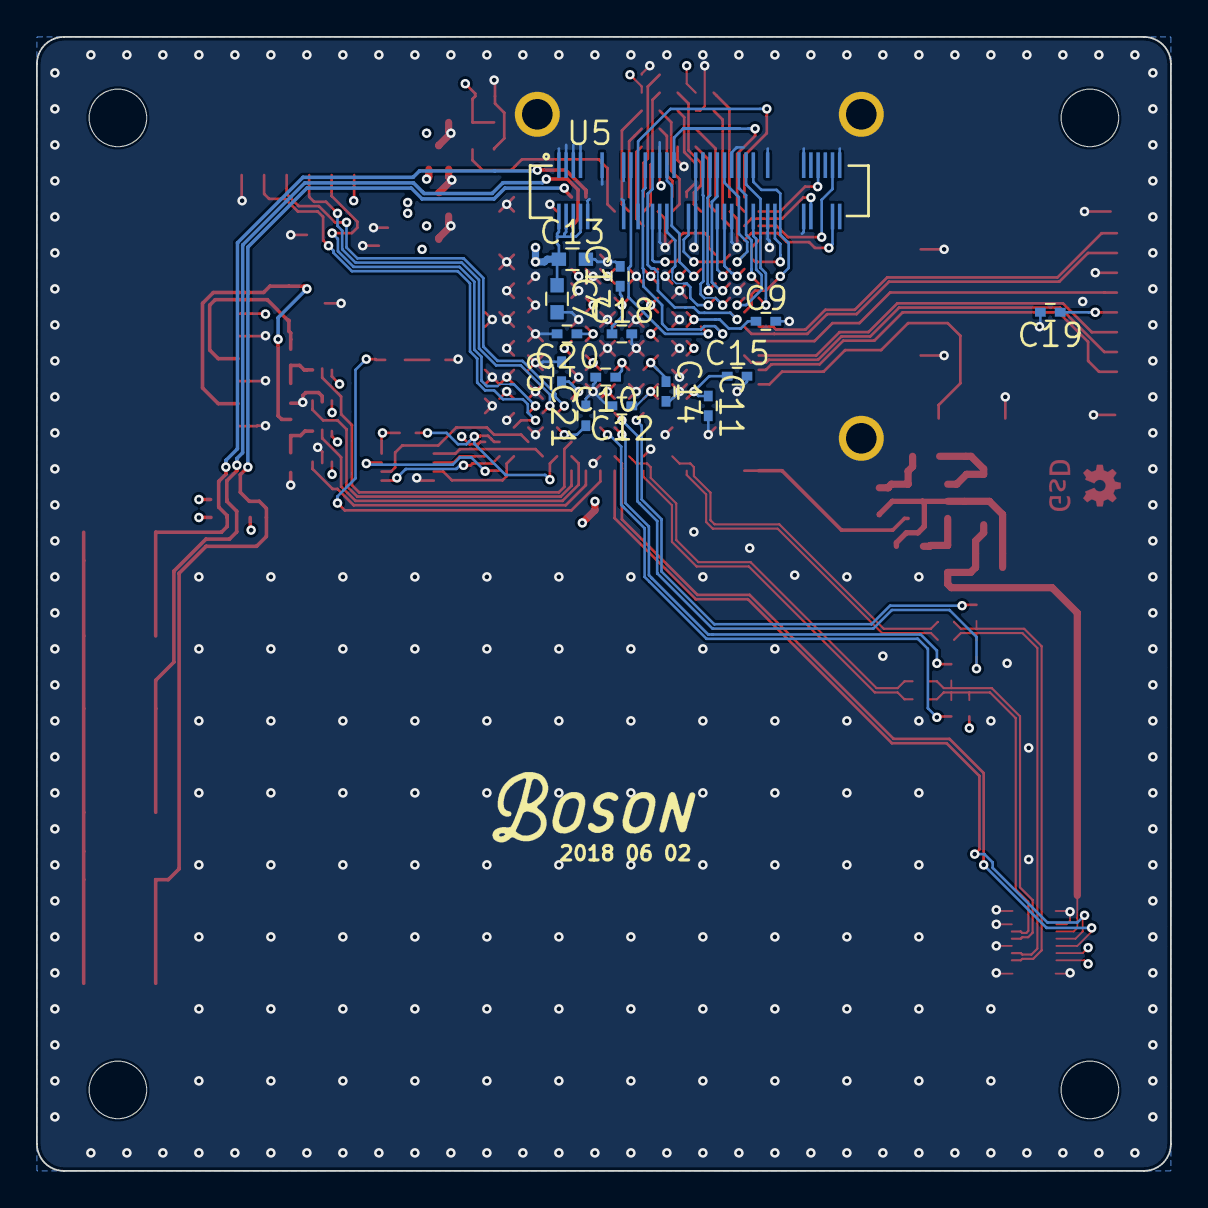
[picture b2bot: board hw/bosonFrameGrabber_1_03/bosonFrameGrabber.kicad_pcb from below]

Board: 4 copper layers, 63.0 x 63.0 mm, 64 parts (15 on the bottom side), 93 nets.

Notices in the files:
hw/programmerAdapter/bfgAdapter.sch:
License: CC-BY-SA 4.0
